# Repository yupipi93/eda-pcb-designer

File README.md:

<div align="center">

# eda-pcb-designer

**One YAML file in → a fabricable PCB out.**

A deterministic, headless **KiCad-9 PCB design pipeline** — spec → schematic →
placement → autorouting → DRC → physical verification → JLCPCB-ready gerbers —
packaged as an installable Python toolkit (`pcb-designer`), with no GUI and no
LLM in the loop.

[Quickstart](#quickstart) · [Hosted API](#3--http-api-hosted--best-for-agents-in-the-cloud) · [The verification gate](#the-physical-verification-gate) · [For AI agents](#for-ai-agents) · [Docs](#documentation)

*Lemon Piano v0.6.0 — pipeline output. Placement, routing, DRC, render and
dimension annotations all generated from one YAML file; the Arduino Nano photo
is composited pin-over-pad by the overlay stage. Designed end-to-end through
the hosted API.*

</div>

---

## The pipeline

```mermaid
flowchart LR
    Y[/"board.yaml<br/>(single source of truth)"/] --> S
    S["schematic<br/>kicad-sch-api"] --> P["place<br/>real layer flips + DRC"]
    P --> R["route<br/>freerouting + GND zone"]
    R --> D["render<br/>DIM · realistic · overlay"]
    D --> V{"verify<br/>anti-mirror gate"}
    V -->|pass| F["fab<br/>gerbers · BOM · pos · zip"]
    V -->|fail| X["⛔ no fab outputs"]
```

Every stage is **headless, idempotent and scriptable**; errors fail fast with
actionable messages. The pipeline calls **no LLM API** — it is a plain,
reproducible Python + KiCad + freerouting toolchain — but it was **built to be
driven safely by an AI coding agent** (Claude, GPT, Gemini, …) as well as by
humans: the agent edits the YAML and drives the CLI, and it cannot reach `fab`
without passing DRC plus a physical-verification gate. See
[`AGENTS.md`](AGENTS.md) for the agent operating protocol.

> [!TIP]
> **🌐 Live hosted API** — **https://pcb-designer.scv.multitecua.com** — no install
> needed. Upload a `.kicad_pcb`, get back an autorouted board, a DRC report,
> raytraced renders or a JLCPCB-ready fab zip:
> ```bash
> curl -F pcb=@board.kicad_pcb https://pcb-designer.scv.multitecua.com/route -o routed.kicad_pcb
> ```

## What it produces

One board, four render styles — all from the same `.kicad_pcb`, all generated
by the `render` stage:

| `bare` | `dim` |
|---|---|
|  |  |
| **`realistic`** | **`overlay`** |
|  |  |

Iterations are versioned, so a board's history reads like a filmstrip:

And it ships real hardware. The **MT1 rocket flight computer** went through
**5 fabricated releases at JLCPCB** — designed entirely by this pipeline inside
the [multi-rocket-avionica](https://github.com/Multitec-UA/multi-rocket-avionica)
project, and vendored here as the worked example ([`projects/mt1/`](projects/mt1/)):

| Pipeline render | The fabricated board |
|---|---|
|  |  |
| *MT1 v0.1.4 — overlay render with real breakout photos* | *The same design, fabricated at JLCPCB and populated* |

## Why

Iterating a PCB by hand in a GUI is slow and unreproducible; letting a generative
model emit `.kicad_pcb` S-expressions directly is dangerous. This toolkit takes a
third path:

- **One YAML per board** captures everything a layout iteration needs (outline,
  placements, pin counts, net numbers, trace widths) — reviewable in a diff.
- **The engine does the mechanical work deterministically**: footprint placement
  with genuine layer flips, freerouting-based autorouting, GND zone + stitching,
  DRC, versioned renders, gerber/BOM/pos exports.
- **Idempotency is law**: any stage can be re-run and converges to the same board.
- **Verification is part of the pipeline, not an afterthought** — see
  [the physical-verification gate](#the-physical-verification-gate) below.

## Install

```bash
git clone https://github.com/yupipi93/eda-pcb-designer
cd eda-pcb-designer
python3 -m venv .venv && source .venv/bin/activate
pip install -e '.[schematic,render,verify,dev]'
pcb-designer --help
```

### System requirements per stage

| Stage | Needs |
|---|---|
| `validate`, `gallery`, `init` | Python ≥ 3.11 only |
| `schematic` | `kicad-sch-api` (extra) + KiCad 9 symbol libraries |
| `place`, `render` | **KiCad 9** (`kicad-cli`) + `poppler-utils` + Pillow |
| `route` | KiCad 9 (`pcbnew` Python module) + **Java 21** + freerouting JAR |
| `verify` | numpy + Pillow (extras) |
| `export3d` | KiCad 9 (`kicad-cli`); component bodies need `kicad-packages3d` (or `--fetch-models`) |
| `fab` | KiCad 9 (`kicad-cli`) |

KiCad 9 install options are documented in [`docs/SETUP.md`](docs/SETUP.md)
(AppImage without root, or `ppa:kicad/kicad-9.0-releases`). The freerouting JAR
is **not** committed — fetch it once, checksum-verified:

```bash
./vendor/fetch-freerouting.sh    # → vendor/freerouting.jar (v2.1.0, 64 MB)
```

**Zero-install alternative** — the Docker image ships the whole toolchain
(KiCad 9 + Java 21 + freerouting + poppler):

```bash
docker build -t eda-pcb-designer .
docker run --rm -w /app eda-pcb-designer pipeline --config examples/mt1.yaml --stages place,render
```

## Quickstart

### 1 · Run the worked example (MT1 flight computer)

```bash
pcb-designer validate --config examples/mt1.yaml
# → OK: MT1 Flight Computer Board (v0.1.4) — 19 placements, 16 through-hole, 100×30 mm board

pcb-designer pipeline --config examples/mt1.yaml --stages place,route,render
# place    → placement + layer flips + GND zone + DRC + renders
# route    → freerouting autoroute + zone fill + stitches (needs Java 21 + JAR)
# render   → PCB-editor-style DIM PNGs                    (needs kicad-cli + pdftocairo)
# export3d → GLB + STEP you can rotate (see "Look at the board in 3D" below)

pcb-designer fab --config examples/mt1.yaml --version v0.1.4
# → projects/mt1/releases/v0.1.4/…zip  (9 gerbers + 2 drill + BOM + pos, JLCPCB-ready)
```

### 2 · Start your own board

```bash
pcb-designer init my-board --template minimal --vendor MyOrg
# → projects/my-board/{kicad,tools,renders,validation,releases}/
# → projects/my-board/my-board.yaml       (the board's single source of truth)
```

Then: create the KiCad project in `projects/my-board/kicad/`, fill in the YAML
(schema: [`docs/CONFIG_REFERENCE.md`](docs/CONFIG_REFERENCE.md), placement
method: [`docs/PLACEMENT_GUIDE.md`](docs/PLACEMENT_GUIDE.md)), and add the
board's orchestrator scripts under `projects/my-board/tools/` — thin wrappers
that bind your board's constants and delegate to the `pcb_designer` package
([`projects/mt1/tools/`](projects/mt1/tools/) is the reference implementation).

### 3 · HTTP API (hosted — best for agents in the cloud)

The stateless HTTP API exposes the engine operations over uploaded board
files — no project checkout, no local KiCad. **No uploaded code is ever
executed**; the server only performs KiCad file surgery and returns the
artefact.

```bash
URL=https://pcb-designer.scv.multitecua.com

# Freerouting-as-a-service: autoroute any .kicad_pcb
curl -F pcb=@board.kicad_pcb "$URL/route" -o routed.kicad_pcb

# DRC report / raytraced renders / JLCPCB-ready fab zip
curl -F pcb=@board.kicad_pcb "$URL/drc" | jq .by_severity
curl -F pcb=@board.kicad_pcb "$URL/render?side=both" -o renders.zip
# render styles: bare | realistic | realistic-dim | dim | overlay
# (overlay: client sends module photos: -F modules=@modules.yaml -F images=@nano.png)

# Rotatable 3D model (?format=glb|step|both) — the service ships the 3D model
# library, so component bodies always resolve here:
curl -F pcb=@board.kicad_pcb "$URL/export3d?format=glb" -o board.glb
curl -F pcb=@board.kicad_pcb "$URL/render?side=top&style=realistic" -o top.png
curl -F pcb=@board.kicad_pcb -F sch=@board.kicad_sch "$URL/fab?version=v1.0.0" -o release.zip

# Validate a YAML config / apply placements
curl --data-binary @examples/mt1.yaml "$URL/validate"
curl -F pcb=@board.kicad_pcb -F config=@board.yaml "$URL/place" -o placed.kicad_pcb
```

`GET /openapi.json` serves the OpenAPI 3 spec (agents self-configure from it);
binary responses become base64 JSON with `?format=json`. Run it yourself with
`make docker-api` or deploy with [`deploy/`](deploy/) (Cloud Run-ready —
production deploys are tag-driven: pushing `pcb-designer-vX.Y.Z` builds and
rolls out automatically via the multitec Terraform repo).

> The **Lemon Piano v0.6.0** board in the hero image was designed end-to-end
> through exactly these endpoints (`/place /route /drc /render /fab`) from its
> product repo, [arduino-lemon-piano](https://github.com/yupipi93/arduino-lemon-piano).

### 4 · Python API

```python
from pcb_designer import load_config
from pcb_designer.placement import place_and_flip

cfg = load_config("examples/mt1.yaml")
text = open(cfg.pcb_path("."), encoding="utf-8").read()
text, updated, missing = place_and_flip(text, {r: p.as_tuple() for r, p in cfg.placements.items()})
```

Every module is importable on its own: `kicad_pcb_io` (depth-aware S-expression
surgery), `placement` (genuine layer flips), `injection`, `routing`,
`autorouter`, `render_dim`, `render_overlay`, `export3d`, `verify`, `fab`.

## The physical-verification gate

The `verify` stage is a **hard gate between routing and fabrication**: a
computer-vision + geometric check that catches mirrored or pin-swapped
footprints by comparing the rendered board against the board's ground-truth
pinout. It exists because **three mirror bugs once reached a real fab order**
(the full story:
[`projects/mt1/docs/POST-MORTEM-001-mirror-rootcause.md`](projects/mt1/docs/POST-MORTEM-001-mirror-rootcause.md)).

| Mounting-hole CV check | Pins-over-pads check |
|---|---|
|  |  |
| *Detected hole centres vs ground truth — deviation 0.000 mm* | *Every module pin proven to sit on its pad* |

If the layout contradicts the ground truth, `verify` exits non-zero and `fab`
never runs. The mirrored board that motivated the gate is kept as a regression
fixture ([`tests/fixtures/mt1-pcb-v0.1.1-buggy.kicad_pcb`](tests/fixtures/)) so
the tests prove the gate still catches it.

## Look at the board in 3D

`export3d` runs in the default pipeline and writes two files per version:
a **`.glb`** (binary glTF — opens in browsers and light viewers) and a
**`.step`** (FreeCAD / Fusion, enclosure design, real fit checks). Both include
tracks, pads, zones, silkscreen and soldermask.

<details>
<summary><b>Viewer recommendations (VS Code, web, native) and the missing-bodies gotcha</b></summary>

**In VS Code — one click.** The repo ships a `.vscode/extensions.json`
recommending [`thingraph.cad-viewer`](https://marketplace.visualstudio.com/items?itemName=thingraph.cad-viewer),
so VS Code offers to install it the first time you open the workspace. Then
double-click the `.glb` — or the `.step` — and drag to rotate. It bundles
`occt-import-js.wasm` (OpenCascade), so its STEP support is a real geometry
kernel.

**Web, nothing to install.** Open <https://3dviewer.net> and drag the `.glb`
in — it renders in your browser, the file is not uploaded to a server.

**Local, lightweight.** [f3d](https://f3d.app) (`sudo apt install f3d`) is a
fast native viewer. There is also KiCad's own 3D viewer (**Alt+3**) if you have
KiCad installed.

**If parts are missing bodies:** component bodies are **not** in the
`.kicad_pcb` — each footprint stores a *path* into the `kicad-packages3d`
library (several GB), and `kicad-cli` skips models it cannot resolve
**silently**. `export3d` detects this and can fetch just the handful of files
your board references (~1–2 MB):

```bash
pcb-designer export3d --config board.yaml --fetch-models
```

The hosted API needs none of this — its image ships the model library.

</details>

## Architecture

```
eda-pcb-designer/
├── src/pcb_designer/        ← the installable package (board-agnostic algorithms)
│   ├── cli.py               ← `pcb-designer` console script
│   ├── config.py            ← ProjectConfig + YAML loader (typed)
│   ├── kicad_pcb_io.py      ← paren-walker primitives for .kicad_pcb surgery
│   ├── placement.py         ← place + genuine F.Cu↔B.Cu flips (mirror-safe)
│   ├── injection.py, routing.py, geometry.py, schematic.py
│   ├── autorouter.py        ← DSN → freerouting → SES → zone fill
│   ├── render_dim.py, export3d.py, fab.py, pipeline.py
│   ├── api.py               ← stateless HTTP API (Flask; `[api]` extra)
│   ├── render_overlay/      ← photorealistic overlay compositor (+ CLI)
│   ├── verify/              ← anti-mirror / anti-pin-swap / mounting-hole gate
│   └── templates/           ← `pcb-designer init` scaffolds
├── deploy/                  ← Cloud Run image (gunicorn) + Cloud Build config
├── docs/                    ← methodology corpus (see below)
├── examples/                ← board configs (mt1.yaml, blank-board)
├── projects/mt1/            ← WORKED EXAMPLE: kicad sources, tools, renders,
│                              validation evidence, fabricated release v0.1.4
├── themes/                  ← KiCad DIM render color themes
├── vendor/                  ← freerouting fetch script (JAR not committed)
└── tests/                   ← unit tests (config, verify, holes, pins, api, 3d)
```

The package/example split is the core design rule: **algorithms live in
`src/pcb_designer/` and take every parameter explicitly; board specifics live in
the board's YAML + `projects/<board>/tools/`**. The pipeline stages
subprocess-call the board's orchestrator scripts (resolved via `project.tools_dir`
in the YAML), so adding a second board never touches the package.

**Where boards live**: a real board belongs to its PRODUCT's repo under
`pcb/` — config, docs, tools, ground-truth, kicad sources, renders,
validation evidence and releases all together — with the board's tools
importing this toolkit as a sibling repo (`../eda-pcb-designer/src`) and
running the generative steps in this repo's Docker image. That is how MT1
lives upstream (`multi-rocket-avionica/pcb/`) and how the Lemon Piano board
lives in `arduino-lemon-piano/pcb/`. The `projects/mt1/` copy here is the
vendored worked example the docs and tests reference — scaffold with
`pcb-designer init`, then move the project folder into the product repo's `pcb/`.

## For AI agents

This repo is designed to be operated by an AI coding agent under a strict
protocol — the agent edits the YAML config and drives the CLI; it never
hand-edits S-expressions for routine iterations, and it cannot reach `fab`
without passing DRC + the physical-verification gate.

- **Entry point**: [`AGENTS.md`](AGENTS.md) — operating manual (reading order,
  hard rules, the iteration loop, stop-and-ask criteria).
- **Per-iteration briefing template**: [`docs/AI_AGENT_PROMPT.md`](docs/AI_AGENT_PROMPT.md).
- **Load-bearing rules**: [`docs/LESSONS_LEARNED.md`](docs/LESSONS_LEARNED.md) —
  24 rules learned from real incidents; breaking them produces boards that pass
  DRC yet crash pcbnew or ship mirrored.

## Documentation

| Doc | What it covers |
|---|---|
| [`docs/METHODOLOGY.md`](docs/METHODOLOGY.md) | The canonical 8-step iteration loop |
| [`docs/CONFIG_REFERENCE.md`](docs/CONFIG_REFERENCE.md) | Full YAML schema |
| [`docs/PLACEMENT_GUIDE.md`](docs/PLACEMENT_GUIDE.md) | How to author a placements table |
| [`docs/LESSONS_LEARNED.md`](docs/LESSONS_LEARNED.md) | 24 load-bearing rules (⭐ read first) |
| [`docs/CONVENTIONS.md`](docs/CONVENTIONS.md) | Naming / footprint / DRC conventions |
| [`docs/PIPELINE.md`](docs/PIPELINE.md) | Stage I/O map + coordinate frames |
| [`docs/MOUNTHOLE_OVERLAY_METHODOLOGY.md`](docs/MOUNTHOLE_OVERLAY_METHODOLOGY.md) | Overlay calibration + mounting-hole verification |
| [`docs/SETUP.md`](docs/SETUP.md) | Machine setup (KiCad 9, Java 21, kicad-mcp) |
| [`docs/FAB_ORDER_GUIDE.md`](docs/FAB_ORDER_GUIDE.md) | JLCPCB quote-to-order walkthrough (real MT1 order) |

> Parts of the methodology corpus are written in Spanish (the project's working
> language); code, identifiers and the agent-facing entry points are in English.

## Development

```bash
make dev    # editable install with all extras
make lint   # ruff check src tests
make test   # pytest
make docker # build the pipeline-in-a-box image
```

CI runs lint + tests on Python 3.11/3.12, validates the example configs,
round-trips a `pcb-designer init` scaffold, builds the Docker image and runs
the MT1 `place,render` stages inside it with a real KiCad 9, and smoke-tests
every HTTP API endpoint against the deploy image.

## Related projects

| repo | what |
|---|---|
| [eda-wirewright](https://github.com/yupipi93/eda-wirewright) | The sibling tool: declarative **wiring-diagram** engine with auto-router + DRC, same engine + hosted-API + agent-protocol pattern |
| [multi-rocket-avionica](https://github.com/Multitec-UA/multi-rocket-avionica) | Where this toolkit was born — the MT1 flight computer's product repo |
| [arduino-lemon-piano](https://github.com/yupipi93/arduino-lemon-piano) | Second production board (`pcb/`), designed end-to-end through the hosted API |

## License

MIT — see [`LICENSE`](LICENSE).

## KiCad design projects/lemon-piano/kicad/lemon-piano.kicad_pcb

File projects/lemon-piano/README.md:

# Lemon Piano V5.5 Board

A fabricable 2-layer KiCad-9 PCB that replaces the
[arduino-lemon-piano](../../../arduino-lemon-piano) **V5.5** breadboard
build — same circuit, same firmware pinout, nothing invented. Seven lemon
touch keys, a ten-LED progress bar, two sensitivity buttons, a passive
buzzer, and the V5.5 **power-entry filter** (TVS + Schottky + CLC pi) that
keeps mains transients from playing phantom notes on a 15–20 mV touch
margin.

| | |
|---|---|
| Top |  |
| Bottom |  |

## At a glance

| Item | Value |
|---|---|
| Outline | 100 × 30 mm, 2-layer FR4, MT1 coordinate frame (x 90–190, y 100–130) |
| MCU | Arduino Nano (ATmega328P), **socketed** — 2×15-pin 2.54 mm rows, mini-USB faces the WEST edge (flash access; USB 5 V stays behind the 1N5817) |
| Keys | 7 lemon lines (A0–A6, 220 Ω pull-ups on B.Cu) + GND clip → labelled 1×8 header, NORTH edge (`G 7 6 5 4 3 2 1`) |
| Display | 10 × 3 mm green LEDs (D2–D11), one ascending run on the SOUTH edge, 220 Ω each on B.Cu |
| Controls | SENS+ (D12) / SENS− (A7 + 10 k pull-up) buttons, SOUTH-east |
| Sound | passive buzzer on D13 |
| Power | `5V IN` screw terminal → P6KE6.8A TVS → 1N5817 → 470 µF‖100 nF → 100 µH → 470 µF‖100 nF → +5 V rail (≈4.7 V, fc ≈ 730 Hz) |
| GND | full B.Cu zone, solid connect on every GND pad, auto island-healing |
| Mounting | 2 × M2 (Ø2.5 drill / Ø5.0 pad+vias) at (95,115) & (185,115) — mirror-symmetric about x=140 |
| Status (v0.1.0) | DRC **0/0/0** · ERC 0/0 · verify_placement / verify_holes / geometry_gate ALL PASS |
| Release | [`releases/v0.1.0/lemon-piano-v0.1.0-fab.zip`](releases/v0.1.0/) — gerbers, drill, BOM, positions |

Netlist ground truth: [docs/NETLIST.md](docs/NETLIST.md) ·
decisions: [docs/DECISIONS.md](docs/DECISIONS.md) ·
state + iteration log: [docs/DESIGN_STATE.md](docs/DESIGN_STATE.md) ·
render history: [renders/INDEX.md](renders/INDEX.md)

## How to regenerate

Everything is generated from [`lemon-piano.yaml`](lemon-piano.yaml) +
[`docs/NETLIST.md`](docs/NETLIST.md); the cloud service does every
pipeline operation that has an endpoint, the Docker image handles the two
generative steps (board/schematic instantiation) and the width/zone
post-pass:

```bash
# one full iteration: build → /place → /route → post → /drc → /render → gates
./projects/lemon-piano/tools/cloud_pipeline.sh v0.1.0

# release (adds cloud /fab, writes releases/<ver>/):
./projects/lemon-piano/tools/cloud_pipeline.sh v0.1.0 --fab

# individual gates:
python3 projects/lemon-piano/tools/verify_placement.py   # anti-mirror/pin-swap
python3 projects/lemon-piano/tools/verify_holes.py       # anchor holes vs GT
python3 projects/lemon-piano/tools/geometry_gate.py      # outline/symmetry/copper
```

All builders are idempotent — re-running produces byte-identical files
(LESSONS_LEARNED §7). The KiCad artefacts live in `kicad/`; every
iteration's DRC report and renders are archived under `validation/` and
`renders/` with their version tag.

## Assembly notes

- Small passives are 0805 HandSolder; R1–R7/R18 and R8–R17 + C2/C4 mount
  on the **bottom** (refs on F.Fab, values in the BOM/pos files).
- Feed `5V IN` from a USB wall charger or bench supply — never the PC
  that flashes the Nano (see the V5.5 powering rules); loop the input
  lead 3–4 turns through a clip-on ferrite for the common-mode path.
- The GND terminal position (`G`, west end of the keys header) is the
  player's hand-held clip line.

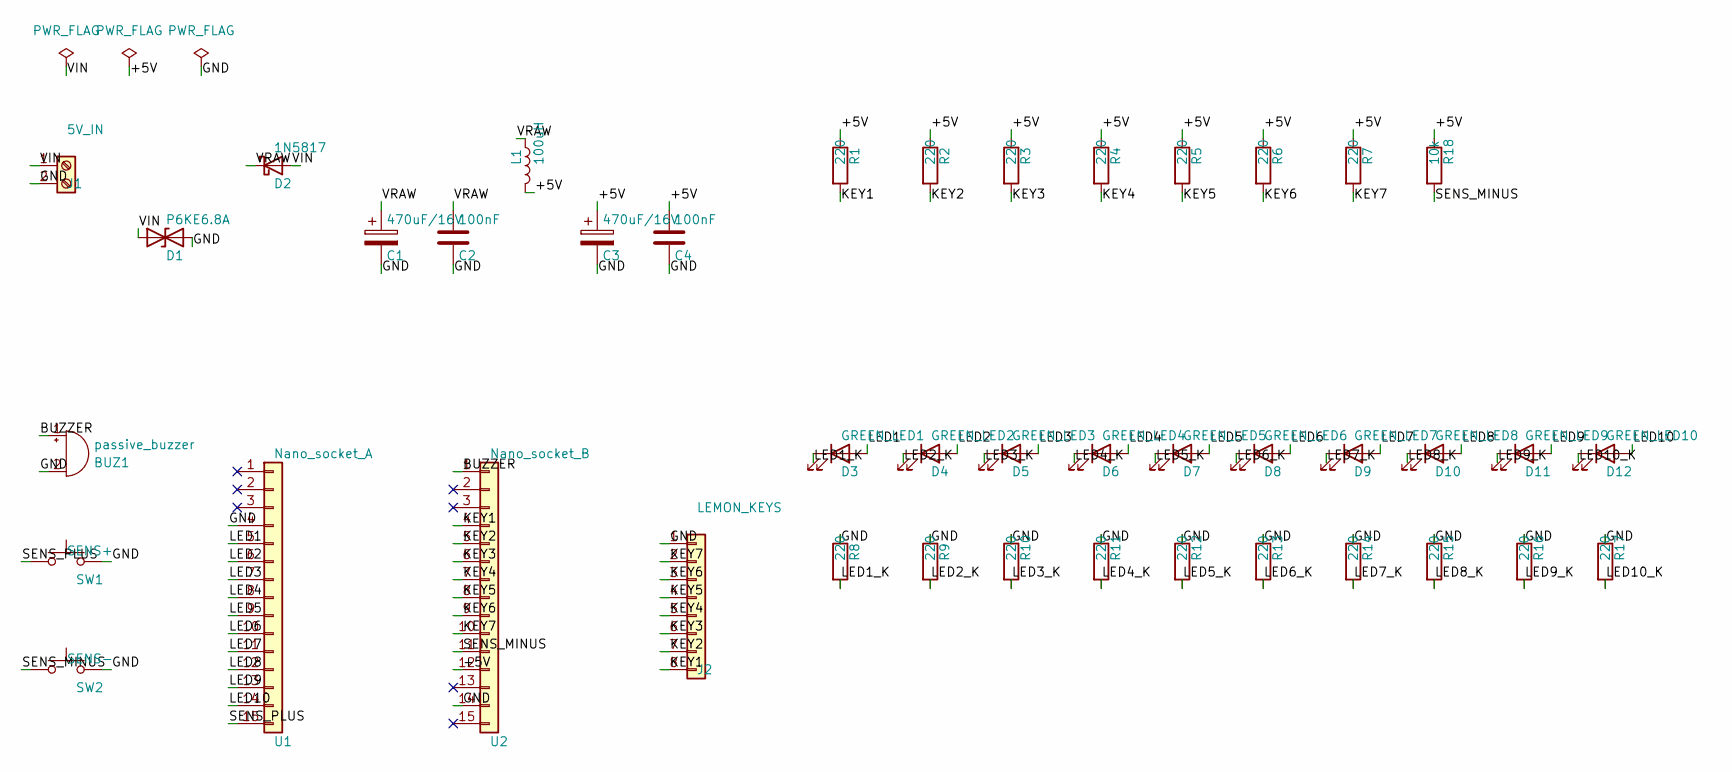
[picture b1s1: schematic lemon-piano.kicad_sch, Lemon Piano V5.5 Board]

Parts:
BUZ1: passive_buzzer; Buzzer_12x9.5RM7.6
C1, C3: 470uF/16V; CP_Radial_D8.0mm_P3.50mm
C2, C4: 100nF; C_0805_2012Metric_Pad1.18x1.45mm_HandSolder
D1: P6KE6.8A; D_DO-15_P5.08mm_Vertical_KathodeUp
D2: 1N5817; D_DO-41_SOD81_P5.08mm_Vertical_AnodeUp
D3: GREEN_LED1; LED_D3.0mm
D4: GREEN_LED2; LED_D3.0mm
D5: GREEN_LED3; LED_D3.0mm
D6: GREEN_LED4; LED_D3.0mm
D7: GREEN_LED5; LED_D3.0mm
D8: GREEN_LED6; LED_D3.0mm
D9: GREEN_LED7; LED_D3.0mm
D10: GREEN_LED8; LED_D3.0mm
D11: GREEN_LED9; LED_D3.0mm
D12: GREEN_LED10; LED_D3.0mm
J1: 5V_IN; TerminalBlock_Phoenix_MKDS-1,5-2-5.08_1x02_P5.08mm_Horizont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
J2: LEMON_KEYS; PinHeader_1x08_P2.54mm_Vertical
L1: 100uH; L_Radial_D8.7mm_P5.00mm_Fastron_07HCP
R1, R2, R3, R4, R5, R6, R7, R8, R9, R10, R11, R12, R13, R14, R15, R16, R17: 220; R_0805_2012Metric_Pad1.20x1.40mm_HandSolder
R18: 10k; R_0805_2012Metric_Pad1.20x1.40mm_HandSolder
SW1: SENS+; SW_PUSH_6mm
SW2: SENS-; SW_PUSH_6mm
U1: Nano_socket_A; PinSocket_1x15_P2.54mm_Vertical
U2: Nano_socket_B; PinSocket_1x15_P2.54mm_Vertical

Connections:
/+5V: C3.1, C4.1, L1.2, R1.1, R2.1, R3.1, R4.1, R5.1, R6.1, R7.1, R18.1, U2.12
/BUZZER: BUZ1.1 (+), U2.1
/GND: BUZ1.2 (-), C1.2, C2.2, C3.2, C4.2, D1.2 (A2), J1.2, J2.1, R8.1, R9.1, R10.1, R11.1, R12.1, R13.1, R14.1, R15.1, R16.1, R17.1, SW1.2, SW2.2, U1.4, U2.14; also elsewhere on the board
/KEY1: J2.8, R1.2, U2.4
/KEY2: J2.7, R2.2, U2.5
/KEY3: J2.6, R3.2, U2.6
/KEY4: J2.5, R4.2, U2.7
/KEY5: J2.4, R5.2, U2.8
/KEY6: J2.3, R6.2, U2.9
/KEY7: J2.2, R7.2, U2.10
/LED1: D3.2 (A), U1.5
/LED1_K: D3.1 (K), R8.2
/LED2: D4.2 (A), U1.6
/LED2_K: D4.1 (K), R9.2
/LED3: D5.2 (A), U1.7
/LED3_K: D5.1 (K), R10.2
/LED4: D6.2 (A), U1.8
/LED4_K: D6.1 (K), R11.2
/LED5: D7.2 (A), U1.9
/LED5_K: D7.1 (K), R12.2
/LED6: D8.2 (A), U1.10
/LED6_K: D8.1 (K), R13.2
/LED7: D9.2 (A), U1.11
/LED7_K: D9.1 (K), R14.2
/LED8: D10.2 (A), U1.12
/LED8_K: D10.1 (K), R15.2
/LED9: D11.2 (A), U1.13
/LED9_K: D11.1 (K), R16.2
/LED10: D12.2 (A), U1.14
/LED10_K: D12.1 (K), R17.2
/SENS_MINUS: R18.2, SW2.1, U2.11
/SENS_PLUS: SW1.1, U1.15
/VIN: D1.1 (A1), D2.2 (A), J1.1
/VRAW: C1.1, C2.1, D2.1 (K), L1.1

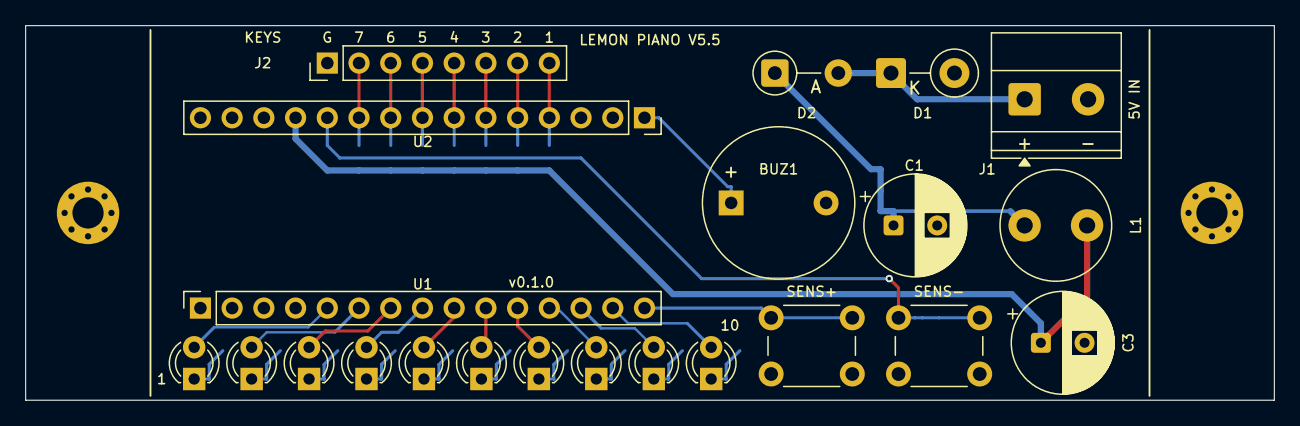
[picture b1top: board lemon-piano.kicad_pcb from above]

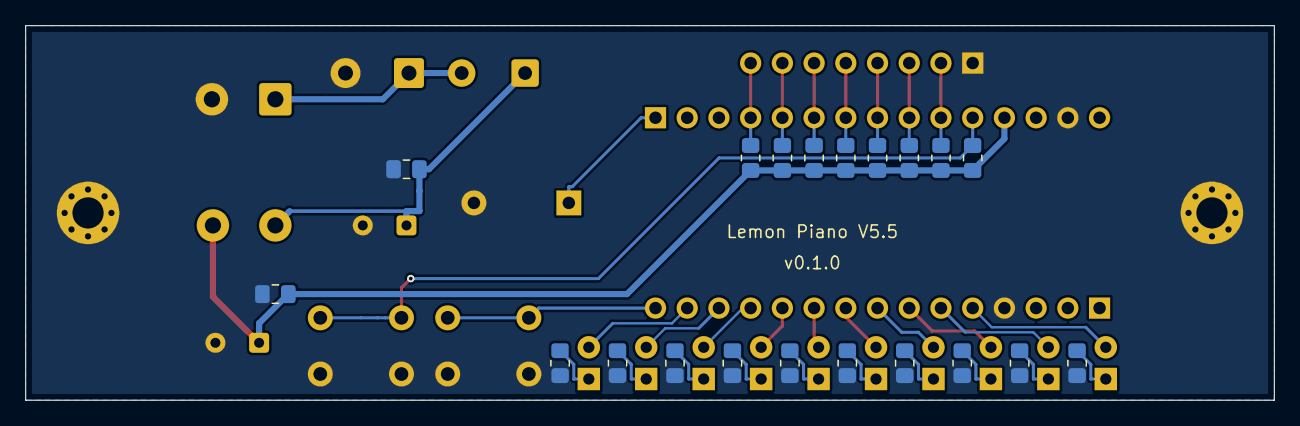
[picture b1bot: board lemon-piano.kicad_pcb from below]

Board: 2 copper layers, 100.0 x 30.0 mm, 44 parts (20 on the bottom side), 34 nets.

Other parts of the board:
H1, H2: M2; MountingHole_2.5mm_Pad_Via

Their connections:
/GND: H1.1, H2.1; also elsewhere on the board

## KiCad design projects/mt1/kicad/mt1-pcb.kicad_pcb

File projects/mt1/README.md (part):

# MT1 — Flight Computer Board

> **Nota**: este directorio es el *worked example* del toolkit standalone [`eda-pcb-designer`](../../README.md), extraído del repo upstream `multi-rocket-avionica`. Aquí se conserva únicamente el último release (**v0.1.4**) con sus renders y evidencia de validación; el historial completo de iteraciones (CHANGELOG, DECISIONS, QUESTIONS, compras/inventario, ~20 iteraciones de renders) vive upstream en [github.com/Multitec-UA/multi-rocket-avionica](https://github.com/Multitec-UA/multi-rocket-avionica) bajo `pcb/projects/mt1/`.

MultitecUA's open-source rocket avionics PCB for the **SURT × SpainRocketry L1 launch (2026-07-18/19)**. 100 × 30 mm KiCad-9 board with a XIAO ESP32-S3 Plus, LSM6DSO32 IMU (±32 g), BMP585 barometer, microSD breakout, y un subsistema de batería v0.1.0 con switch de armado, jumper externo y sensor de voltaje on-board. Diseñado end-to-end con el toolkit reusable [`pcb-designer`](../../) — MT1 es su ejemplo dogfood.

## At a glance

| | |
|---|---|
| Current revision | **v0.1.4** (fabricada 2026-06-18; v0.1.0-battery-power fue el primer release fabricado) |
| Board size | 100 × 30 mm (10 mm left anchor + 70 mm electronic + 20 mm right anchor) |
| Estimated weight | ~38 g (PCB + populated breakouts + battery) |
| MCU | Seeed XIAO ESP32-S3 Plus (240 MHz, 8 MB PSRAM, WiFi + BLE) |
| IMU | Adafruit LSM6DSO32 (±32 g, ±2000 °/s) |
| Barometer | Adafruit BMP585 (30 – 1250 hPa, ±0.06 hPa) |
| Storage | microSD breakout (SDIO 1-bit) |
| Battery | LiPo 602535 1S 500 mAh, JST-PH 2 mm |
| Battery management | SW1 SPDT (armado) + J2 (jumper externo paralelo) + R3/R4 + C8 (sensor VBAT_SENSE → D0/ADC1_CH0) |
| Footprints v0.1.0 | 19 (5 sockets módulos + J4 proto + 6 mounting holes + 7 subsistema batería) |
| Last ERC | ✅ 0 errors, 0 warnings (v0.1.0, 2026-05-22) |
| Last DRC | ✅ 0 errores · 0 unconnected · 77 warnings cosméticos (v0.1.4, 2026-06-18) — full report en [`validation/drc-v0.1.4.json`](validation/drc-v0.1.4.json) |
| Tests | ✅ 42/42 (v0.1.4) |
| Fab status | ✅ v0.1.4 empaquetada para fab (gerbers + drill + BOM + pos en [`releases/v0.1.4/`](releases/v0.1.4/)); pedido v0.1.0: JLCPCB 5 boards + LCSC `WM2605230017` (histórico, en el repo upstream) |

## Renders v0.1.4

### Vista DIM (PCB-editor-style, alta nitidez de trazas)

| Front (F.Cu) | Back (B.Cu) |
|:---:|:---:|
|  |  |

Renders auto-generados por [`tools/render_dim.py`](tools/render_dim.py) con themes en [`themes/dim-{front,back}.json`](../../themes/). En *dim-front* la cara F.Cu se ve nítida (rojo) sobre fondo oscuro; en *dim-back* es la B.Cu (cian) la prominente. El plano GND continuo de la B.Cu llena toda la cara inferior con thermal reliefs alrededor de los pads GND.

### Vista 3D fotorrealista (KiCad pcbnew + overlay)

| Top | Bottom |
|:---:|:---:|
|  |  |

Composición de [`src/pcb_designer/render_overlay/cli.py`](../../src/pcb_designer/render_overlay/cli.py) que toma los renders 3D base y superpone fotos físicas de los breakouts (XIAO, microSD en top; LSM6, BMP585 en bottom). El config de módulos vive en [`overlays/modules.yaml`](overlays/modules.yaml) y las fotos en `overlays/component-images/`. **Obligatorio** para cualquier entregable v0.X.X (regla MultitecUA).

### Vistas 3D sin overlay

Renders crudos en [`renders/`](renders/): `v0.1.4-top.png` y `v0.1.4-bottom.png`. Catálogo en [`renders/INDEX.md`](renders/INDEX.md) — el histórico completo (~16 versiones × 4 vistas) vive en el repo upstream —, regenerable con `pcb-designer gallery --renders-dir projects/mt1/renders`.

## Cómo está organizado el board

### Mapa físico (vista top)

```
                            x=100              x=170
       LEFT ANCHOR (x=90)   │  ELECTRONIC ZONE  │  RIGHT ANCHOR (x=190)
              │             │   70 × 30 mm      │             │
   y=100  ┌───┴───┬─────────┴───────────────────┴─────────┬───┴───┐
          │       │ ░░░ BATTERY STRIP (y=104) ░░░ ░░░░░░░ │       │
          │       │ J1   SW1   J2   R3 R4 C8   J5        │  H1   │
          │       │ JST  ON   ext  ╰─VBAT_SENSE╯  → BAT+ │  H2   │
          │       │                                       │       │
          │  H5   │            J4 proto (8-pin)           │       │
          │       │                                       │       │
          │       │           U1 XIAO  U5 XIAO            │  H3   │
          │       │           (left)   (right)            │  H4   │
          │       │             ╰─ U4 microSD ─╯          │       │
          │  H6   │                                       │       │
   y=130  └───┬───┴───────────────────────────────────────┴───┬───┘
              │              ↑ service edge                   │
                          (USB-C XIAO + microSD slot
                           asoman por aquí)
```

En B.Cu (vista trasera) sólo cuelgan **U2 (LSM6DSO32 IMU)** alineado con el eje longitudinal del cohete y **U3 (BMP585 barómetro)** en la esquina contraria. El resto de la cara es plano GND continuo (`(zone)` rellenado por `ZONE_FILLER` con thermal reliefs).

### Bloques funcionales

```mermaid
flowchart LR
  LIPO[("LiPo 602535<br/>500 mAh")]
  J1[("J1 JST-PH<br/>battery in")]
  SW1{{"SW1 SPDT<br/>(arming)"}}
  J2{{"J2 1×2<br/>(ext jumper)"}}
  J5[("J5 1×2<br/>→ XIAO BAT+")]
  XIAO["U1+U5 XIAO ESP32-S3 Plus<br/>(MCU socket, 14 pines útiles)"]
  IMU["U2 LSM6DSO32 (B.Cu)<br/>I²C ±32 g IMU"]
  BARO["U3 BMP585 (B.Cu)<br/>I²C barómetro"]
  SD["U4 microSD<br/>SDIO 1-bit"]
  ADC{{"D0 ADC1_CH0<br/>VBAT_SENSE"}}
  PROTO["J4 1×8 proto<br/>(D1-D3 libres + DBG + 3V3 + GND)"]

  LIPO --> J1
  J1 -- BAT_P --> SW1
  J1 -- BAT_P --> J2
  SW1 -- BAT_SW --> J5
  J2 -- BAT_SW --> J5
  J5 -- "BAT+" --> XIAO
  SW1 -- BAT_SW --> ADC
  XIAO -- "+3V3" --> IMU & BARO & SD
  XIAO -- I²C --> IMU & BARO
  XIAO -- SDIO --> SD
  XIAO -- pins libres --> PROTO
```

### Tabla de componentes (v0.1.0)

| Ref | Componente | Capa | Función |
|---|---|---|---|
| **U1** | XIAO ESP32-S3 Plus — socket izquierdo (pines D0..D6 + GND) | F.Cu | MCU. Pin 1 (= D0) → VBAT_SENSE/ADC1. USB-C asoma al borde y=130. |
| **U5** | XIAO ESP32-S3 Plus — socket derecho (pines D7..D10 + BAT+ + 3V3) | F.Cu | MCU (mismo módulo). Pin 6 = BAT+ → recibe `BAT_SW`. Pin 7 = +3V3 (regulado interno). |
| **J4** | Proto header 1×8 vertical sobre los XIAO | F.Cu | Test points + pines libres: J4.1 = VBAT_SENSE, J4.2-4 = D1..D3 libres, J4.5 = DBG_TX, J4.6 = DBG_RX, J4.7 = +3V3, J4.8 = GND. |
| **U2** | Adafruit LSM6DSO32 — IMU 6DoF ±32 g | **B.Cu** | I²C @ 0x6A. Body alineado con eje longitudinal del cohete (rot=90). |
| **U3** | Adafruit BMP585 — barómetro 30-1250 hPa | **B.Cu** | I²C @ 0x47. Junto al LSM6 para minimizar trazas I²C. |
| **U4** | microSD breakout — slot estándar | F.Cu | SDIO 1-bit. Slot asoma al borde y=130 (tarjeta se extrae sin desmontar el board). |
| **J1** | JST-PH 2-pin horizontal — entrada LiPo | F.Cu | Pin 1 = `BAT_P` (raw battery), Pin 2 = `GND`. Compatible con `LiPo 602535`. |
| **SW1** | SPDT slide switch (CK OS102011MS2Q) — armado | F.Cu | Pad 1 común = `BAT_P`. Pad 2 (throw A, ON) = `BAT_SW`. Pad 3 (throw B, OFF) = **NC** (intencionalmente). |
| **J2** | Header 1×2 vertical — bypass / botón externo | F.Cu | Paralelo a SW1: Pin 1 = `BAT_P`, Pin 2 = `BAT_SW`. |
| **J5** | Header 1×2 vertical — tap-out a XIAO | F.Cu | Pin 1 = `BAT_SW` (cable manual al pad BAT+ del XIAO en U5), Pin 2 = `GND`. |
| **R3** | 100 kΩ 0805 1% — top del divisor VBAT | F.Cu | Entre `BAT_SW` y `VBAT_SENSE`. |
| **R4** | 100 kΩ 0805 1% — bottom del divisor VBAT | F.Cu | Entre `VBAT_SENSE` y `GND`. Junto con R3 forma 1:2 ÷. |
| **C8** | 100 nF 0805 X7R 50V — filtro ADC | F.Cu | `VBAT_SENSE` ↔ `GND`. Cap RC anti-ruido en la entrada del ADC. |
| **H1..H4** | Mounting holes M2 NPTH (anchor derecho, patrón 2×2) | F.Cu | Fijación estructural al airframe (lado fijo al cohete). |
| **H5, H6** | Mounting holes M2 NPTH (anchor izquierdo, en columna) | F.Cu | Fijación estructural (lado opuesto). |

> Componentes históricos retirados en v0.0.12 (BUZ1 buzzer, SW2/SW3 botones, LED+R de UI, F1 PTC, D3 TVS, C1 22 µF, C2..C7 de decoupling, TP1..TP7 test points discretos) — catálogo + criterio de re-incorporación en `docs/REMOVED_COMPONENTS.md` (en el repo upstream).

## Sistema de alimentación detallado (v0.1.0)

Esta es la novedad principal del release v0.1.0 — antes el XIAO se alimentaba directamente desde el conector JST sin armado ni telemetría de batería. Ahora hay tres formas de controlar el encendido y una lectura analógica del voltaje de batería en tiempo real.

### Topología eléctrica

```
                    ┌───────── SW1 (ON) ─────────┐
   LiPo+ ─J1.1─ BAT_P ─┤                            ├── BAT_SW ──┬── J5.1 ──► XIAO BAT+ (U5 pin 6)
                       │                            │             │
                       └───── J2.1 ── ext ── J2.2 ──┘             │
                                                                  │
                                    ┌─── R3 100kΩ ───┬── VBAT_SENSE ──► XIAO D0 (ADC1_CH0)
                                    │                │                    │
                                    │                ├── R4 100kΩ ──┐    │
                                    │                └── C8 100nF ──┤    │ (también expuesta en
                                    │                               │    │  J4.1 como test point)
   LiPo− ─J1.2─ GND ────────────────┴───────────────────────────────┴────┴──► GND plane (B.Cu)
                                                          J5.2 ──────────┘
```

Pad-map del SW1 (footprint `SW_Slide_SPDT_Straight_CK_OS102011MS2Q`):

```
       ┌──────────────┐
   1 ──┤●  common     │   ← BAT_P (entrada desde J1.1)
   2 ──┤●  throw A    │   ← BAT_SW (cuando la barrita está en posición ON)
   3 ──┤●  throw B NC │   ← OFF: pad sin conectar (sin carga parasitaria)
       └──────────────┘
```

### 1. Switch principal SW1 (armado / disconnect)

**Componente físico**: SPDT slide switch C&K `OS102011MS2Q` THT, actuador horizontal accesible desde el borde del PCB. Se usa como **interruptor de armado**: se desliza a la posición ON el día del vuelo, off durante transporte/integración.

**Lógica**:
- Posición **ON** (barrita hacia pad 2): cierra `BAT_P` → `BAT_SW` → la batería energiza el XIAO vía J5.
- Posición **OFF** (barrita hacia pad 3): pad 3 está deliberadamente sin conectar (`NC`). El circuito de batería queda completamente abierto: cero corriente parásita en la balanza R3/R4 (el ADC no tiene a qué medir porque `BAT_SW` está flotante).

**Razón de diseño** (ADR-014, ver `docs/DECISIONS.md` en el repo upstream): un slide SPDT es preferible a un push-button latching porque (a) es visualmente inequívoco — el ojo distingue ON/OFF a distancia — y (b) no se actua por accidente con un golpe lateral. Coste: 1 € en LCSC vs 0.10 € de un push, asumido.

### 2. Jumper auxiliar J2 (bypass / botón exterior)

**Header 1×2 PinHeader 2.54 mm** colocado eléctricamente en **paralelo** a SW1: pin 1 = `BAT_P` (entrada), pin 2 = `BAT_SW` (salida).

**Tres modos de uso:**

1. **Jumper colocado**: J2 cortocircuita `BAT_P` ↔ `BAT_SW`. El sistema queda **siempre encendido** ignorando SW1. Útil en mesa para evitar tocar SW1 a cada flash/depuración.

2. **Botón exterior conectado**: a J2 se le cablean dos hilos hacia un pulsador exterior montado en el cuerpo del cohete (típicamente un pulsador estanco accesible sin desmontar la ojiva). El pulsador queda **en paralelo con SW1**, así que sirve para encender desde fuera sin desarmar nada. Cualquiera de los dos caminos cerrado → sistema activo.

3. **Vacío**: comportamiento por defecto, SW1 es el único control.

> **Nota importante sobre seguridad eléctrica**: con SW1 OFF y J2 sin jumper, el board está completamente desconectado de la batería — esto es lo que se documenta como "safe state" para integración con pirotecnia o manipulación cerca del LiPo. Para forzar el "siempre on" cuando se vuela con telemetría continua, coloca un jumper en J2 **antes** del flight.

### 3. Sensor de voltaje on-board (VBAT_SENSE)

**Objetivo**: telemetría en tiempo real del estado de carga de la batería, leíble por software sin instrumentación externa. La red `VBAT_SENSE` se conecta directamente a `D0` del XIAO (= `GPIO1`, multiplexado a `ADC1_CH0`).

**Circuito**: divisor resistivo 1:2 con filtro RC en la salida.

| Componente | Valor | Función |
|---|---|---|
| R3 | 100 kΩ 0805 1% | Rama superior del divisor (BAT_SW → VBAT_SENSE) |
| R4 | 100 kΩ 0805 1% | Rama inferior (VBAT_SENSE → GND) |
| C8 | 100 nF 0805 X7R | Cap de filtrado en VBAT_SENSE → GND |

**Cálculo del rango**:

```
V_adc = V_BAT × R4 / (R3 + R4) = V_BAT × 100k / 200k = V_BAT × 0.5

Battery range  →  ADC input voltage
  4.20 V (full)  →  2.10 V
  3.70 V (nom)   →  1.85 V
  3.30 V (cutoff) →  1.65 V
  3.00 V (deep low) →  1.50 V
```

Con el ESP32-S3 en su atenuación recomendada (`ADC_ATTEN_DB_11`, rango ≈ 0–3.1 V), todo el envolvente del LiPo cae dentro del rango lineal del ADC con margen al techo. La firma del divisor consume `4.2 V / 200 kΩ = 21 µA` constante mientras el sistema está armado (despreciable frente al consumo del XIAO, decenas de mA).

**Por qué los 100 nF de C8**: el ADC del ESP32-S3 muestrea con un capacitor interno; pico de corriente en el instante de muestreo. C8 actúa como reservorio local y promedia ruido conmutado del rail de batería (especialmente importante cuando el WiFi del XIAO entra en transmisión y mete picos de hasta 300 mA en `BAT_P`).

**Cómo leerlo en firmware** (referencia, no incluido en este repo):

```cpp
#include <driver/adc.h>
adc1_config_width(ADC_WIDTH_BIT_12);
adc1_config_channel_atten(ADC1_CHANNEL_0, ADC_ATTEN_DB_11);
int raw = adc1_get_raw(ADC1_CHANNEL_0);                 // 0..4095
float v_adc = raw * 3.1f / 4095.0f;
float v_bat = v_adc * 2.0f;                             // 1:2 divider
```

**Test point**: `VBAT_SENSE` también está expuesta en **J4.1** (primer pin del header proto sobre el XIAO), así que se puede medir con multímetro sin pinchar el divisor. Útil para calibrar el factor 0.5 contra el voltaje real de la batería al integrar el sistema.

### 4. Conexión al XIAO — J5 y los pads BAT+/BAT−

El XIAO ESP32-S3 Plus tiene en su parte trasera dos pads **TH** marcados `BAT+` y `BAT−` (cara de las pistas, no headers). El XIAO en sí no tiene un PMIC de carga ni un boost — `BAT+` va directamente a la entrada del regulador interno LDO del XIAO. Eso significa que **la batería se cablea manualmente** de J5 a esos pads con dos hilos cortos:

- **J5.1** (`BAT_SW`) → pad `BAT+` del XIAO (en U5).
- **J5.2** (`GND`) → pad `BAT−` del XIAO (en U5).

> Esta es una limitación del XIAO ESP32-S3 Plus que evaluamos al elegirlo: no tiene contactos de batería accesibles desde el header SMT principal. La opción de poner un footprint pogo o spring-loaded se descartó por coste/área. Dos hilos manuales a J5 son robustos y reversibles.

### 5. Pinout completo del XIAO en MT1

```
                    ┌──────────────────────┐
        VBAT_SENSE──┤ D0  (GPIO1, ADC1_CH0)│
                    │ D1  (GPIO2)          │── J4.2 (libre, breakout)
                    │ D2  (GPIO3)          │── J4.3 (libre, breakout)
                    │ D3  (GPIO4)          │── J4.4 (libre, breakout)
            I2C_SDA─┤ D4  (GPIO5)          │── U2 + U3 (SDA bus)
            I2C_SCL─┤ D5  (GPIO6)          │── U2 + U3 (SCL bus)
             DBG_TX─┤ D6  (GPIO7, UART)    │── J4.5
             DBG_RX─┤ D7  (GPIO20, UART)   │── J4.6
           SDIO_D0─┤ D8  (GPIO8)          │── U4 microSD DAT0
           SDIO_CLK─┤ D9  (GPIO9)          │── U4 microSD CLK
           SDIO_CMD─┤ D10 (GPIO10)         │── U4 microSD CMD
                    │                      │
              BAT+──┤ pad TH trasero       │── J5.1 (BAT_SW)
              BAT−──┤ pad TH trasero       │── J5.2 (GND)
              +3V3──┤ pin 7 (regulado int.)│── U2 + U3 + U4 (rail sensores) + J4.7
                    └──────────────────────┘
```

Las redes activas en v0.1.0 son **15** (ver `docs/DESIGN_STATE.md §3 Nets` para conteos y la traza completa). Las nets críticas en términos de ruido/longitud son I²C_SDA/SCL (sensores) y las SDIO (microSD); ambas viven en F.Cu con plano GND continuo en B.Cu actuando de retorno limpio.

## Cómo regenerar el board

El board es paramétrico: cada constante vive en [`examples/mt1.yaml`](../../examples/mt1.yaml) (sección `geometry`, `placements`, `pin_counts`, `pad_half`, `nets`, `routing`). Regenerar MT1 end-to-end es un único comando:

```bash
# (desde la raíz del repo, una vez por máquina) venv local del paquete
python3 -m venv .venv
source .venv/bin/activate
python3 -m pip install -e '.[schematic,render,dev]'

# Pipeline completo:
pcb-designer pipeline \
    --config examples/mt1.yaml \
    --stages place,route,render

# Empaquetar release (gerbers + drill + BOM + pos + zip):
pcb-designer fab \
    --config examples/mt1.yaml \
    --version v0.1.4
```

Equivalente paso-a-paso vía los orquestadores MT1 (útil para flags como `--dry-run` o `--version`):

```bash
python3 projects/mt1/tools/build_schematic.py    # regenera .kicad_sch desde spec
python3 projects/mt1/tools/inject_battery.py     # inyecta subsistema batería v0.1.0
python3 projects/mt1/tools/place_components.py   # placement + flip + DRC + 3D + DIM renders
python3 projects/mt1/tools/run_autorouter.py     # freerouting + GND zone fill
python3 projects/mt1/tools/render_dim.py --version v0.1.4
python3 src/pcb_designer/render_overlay/cli.py \
    --version v0.1.4                    # ⭐ overlay fotorrealista (obligatorio)
pcb-designer fab \
    --config examples/mt1.yaml \
    --version v0.1.4
```

El paso de overlay es **obligatorio** para cualquier entregable v0.X.X de este proyecto — nunca lo saltes.

## Contexto aerodinámico (justifica el sensor IMU)

Simulación OpenRocket en `simulation/` (en el repo upstream) del cohete MT1 (motor Cesaroni 232H123-14A) predice apogeo 586 m, velocidad pico 115 m/s, **aceleración pico 7.7 g**. El IMU se eligió con margen (LSM6DSO32 ±32 g) para que el envolvente de vuelo quede holgadamente dentro del rango lineal sin saturar.

## Inventario físico y etiquetado

`inventory-labels.html` (en el repo upstream) es un documento HTML auto-contenido (abrible en navegador) con las etiquetas imprimibles de cada bin del kit de partes. Genera un PDF de bin labels listo para pegar en cajas Hammond o sobre el banco de trabajo. El contenido del inventario "fuente de verdad" vive en `docs/INVENTORY.md` (también en el repo upstream; cantidades disponibles + códigos LCSC/Digikey + ubicación física en el laboratorio).

> Para imprimir las etiquetas: `xdg-open pcb/projects/mt1/inventory-labels.html` (desde el repo upstream) → Ctrl+P → "Save as PDF".

## Releases y fabricación

> **Nota**: el release vigente es **v0.1.4** (fabricada 2026-06-18; DRC 0 errores / 77 warnings; 42/42 tests) — ver [`releases/v0.1.4/`](releases/v0.1.4/) y sus [notas de release](releases/v0.1.4/README.md).

`releases/v0.1.0/` (histórico, en el repo upstream) contiene el primer corte fabricado:

| Archivo | Contenido |
|---|---|
| `README.md` | Notas del release (revisión, fecha, links a DRC, decisión de fab). |
| `gerbers/` | 9 capas Gerber (F/B Cu, Paste, Mask, Silkscreen, Edge Cuts) + 2 drills (NPTH, PTH) + `.gbrjob`. |
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
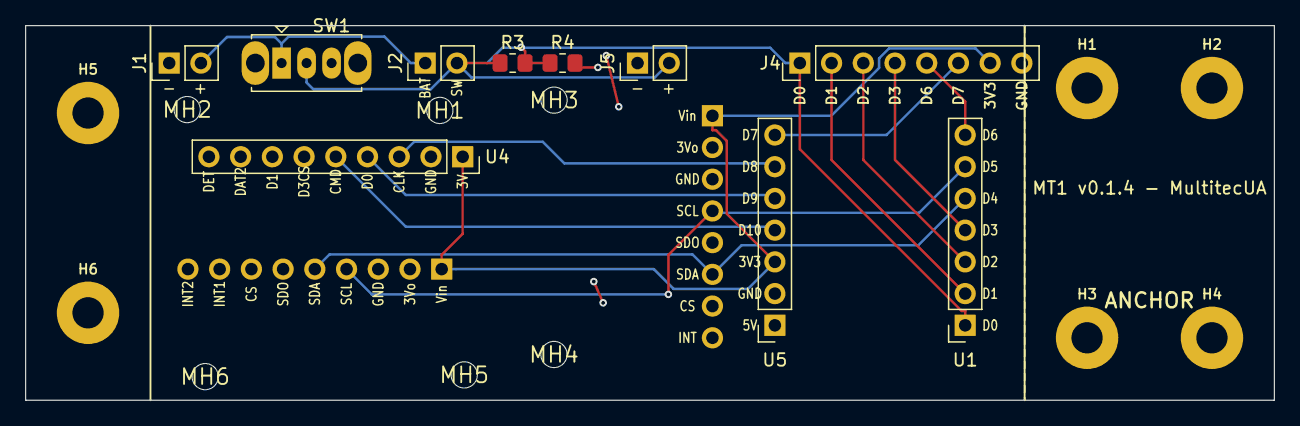
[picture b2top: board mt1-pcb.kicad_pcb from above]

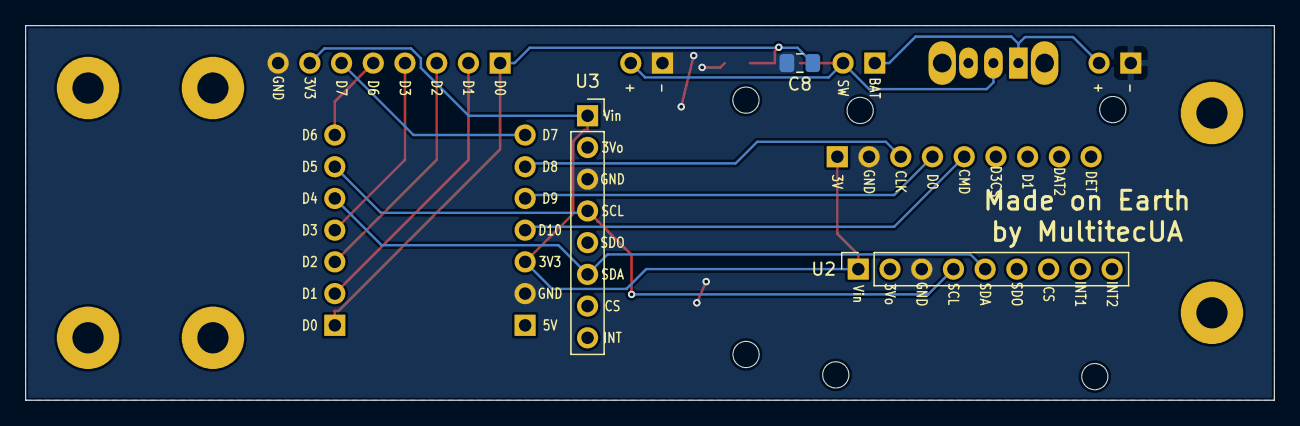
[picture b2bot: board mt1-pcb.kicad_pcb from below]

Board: 2 copper layers, 100.0 x 30.0 mm, 25 parts (3 on the bottom side), 15 nets.

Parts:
C8: C_0805_2012Metric_Pad1.18x1.45mm_HandSolder
H1, H2, H3, H4, H5, H6: MountingHole; MountingHole_2.5mm_Pad_Via
J1, J5: Conn_01x02; PinHeader_1x02_P2.54mm_Vertical
J2: PinHeader_1x02_P2.54mm_Vertical
J4: proto_header; PinHeader_1x08_P2.54mm_Vertical
MH1, MH2, MH3, MH4, MH5, MH6: MT_MountHole_M2
R3, R4: R_0805_2012Metric_Pad1.20x1.40mm_HandSolder
SW1: SW_Slide_SPDT_Straight_CK_OS102011MS2Q
U1: XIAO_left_socket; PinSocket_1x07_P2.54mm_Vertical
U2: LSM6DSO32_socket; PinSocket_1x09_P2.54mm_Vertical
U3: BMP585_socket; PinSocket_1x08_P2.54mm_Vertical
U4: microSD_socket; PinSocket_1x09_P2.54mm_Vertical
U5: XIAO_right_socket; PinSocket_1x07_P2.54mm_Vertical

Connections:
/+3V3: J4.7, U2.1, U3.1, U4.1, U5.3
/BAT_P: J1.2, J2.1, SW1.1
/BAT_SW: J2.2, J5.2, R3.1, SW1.2
/BTN2: J4.2, U1.2
/DBG_RX: J4.6, U5.7
/DBG_TX: J4.5, U1.7
/GND: C8.2, J1.1, J4.8, J5.1, R4.2, U2.3, U3.3, U4.2, U5.2
/I2C_SCL: U1.6, U2.4, U3.4
/I2C_SDA: U1.5, U2.5, U3.6
/LED1: J4.3, U1.3
/LED2: J4.4, U1.4
/SDIO_CLK: U4.3, U5.6
/SDIO_CMD: U4.5, U5.4
/SDIO_D0: U4.4, U5.5
/VBAT_SENSE: C8.1, J4.1, R3.2, R4.1, U1.1

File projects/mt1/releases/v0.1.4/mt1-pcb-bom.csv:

"Reference","Value","Footprint","QUANTITY"
"C8","100nF","Capacitor_SMD:C_0805_2012Metric_Pad1.18x1.45mm_HandSolder","1"
"J1","LiPo_battery","Connector_JST:JST_PH_S2B-PH-K_1x02_P2.00mm_Horizontal","1"
"J2","ext_switch_header","Connector_PinHeader_2.54mm:PinHeader_1x02_P2.54mm_Vertical","1"
"J4","proto_header","Connector_PinHeader_2.54mm:PinHeader_1x08_P2.54mm_Vertical","1"
"J5","XIAO_BAT_wires","Connector_PinHeader_2.54mm:PinHeader_1x02_P2.54mm_Vertical","1"
"R3,R4","100k","Resistor_SMD:R_0805_2012Metric_Pad1.20x1.40mm_HandSolder","2"
"SW1","arming_switch","Button_Switch_THT:SW_Slide_SPDT_Straight_CK_OS102011MS2Q","1"
"U1","XIAO_left_socket","Connector_PinSocket_2.54mm:PinSocket_1x07_P2.54mm_Vertical","1"
"U2","LSM6DSO32_socket","Connector_PinSocket_2.54mm:PinSocket_1x09_P2.54mm_Vertical","1"
"U3","BMP585_socket","Connector_PinSocket_2.54mm:PinSocket_1x08_P2.54mm_Vertical","1"
"U4","microSD_socket","Connector_PinSocket_2.54mm:PinSocket_1x09_P2.54mm_Vertical","1"
"U5","XIAO_right_socket","Connector_PinSocket_2.54mm:PinSocket_1x07_P2.54mm_Vertical","1"

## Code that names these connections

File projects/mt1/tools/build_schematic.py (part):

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    R3, R4 (100 kΩ 0805 HandSolder) – 1:2 divider
    C8 (100 nF 0805 HandSolder)     – RC filter at the ADC input

  Net rename: BTN1 → VBAT_SENSE. The pin used to be the BTN1 line in
  the original plan but SW2 (the button) was scoped out; D0 is now
  driven by the divider midpoint.

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        # D0 / GPIO1 / ADC1_CH0: in v0.1.0 this pin reads the LiPo voltage
        # via the R3/R4 divider midpoint (was BTN1 in pre-v0.1.0 plans).
        "1": ("VBAT_SENSE", "left"),
        "2": ("BTN2",    "left"),  # D1 / GPIO2
        "3": ("LED1",    "left"),  # D2 / GPIO3
        "4": ("LED2",    "left"),  # D3 / GPIO4
        "5": ("I2C_SDA", "left"),  # D4 / GPIO5
        "6": ("I2C_SCL", "left"),  # D5 / GPIO6
        "7": ("DBG_TX",  "left"),  # D6 / GPIO43 — routed to J4 in v0.0.14
    })

    # U5 — XIAO RIGHT header (7 pins): 5V, GND, 3V3, D10, D9, D8, D7
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        "1": (None, None),          # 5V (USB) — no consumer in slim design (NC)
        "2": ("GND",      "right"),
        "3": ("+3V3",     "right"),
        "4": ("SDIO_CMD", "right"), # D10 / GPIO9
        "5": ("SDIO_D0",  "right"), # D9  / GPIO8
        "6": ("SDIO_CLK", "right"), # D8  / GPIO7
        "7": ("DBG_RX",   "right"), # D7 / GPIO44 — routed to J4 in v0.0.14
    })

    # ==================================================================
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        # divider midpoint + XIAO D0). Probe with a multimeter to read
        # raw ADC input voltage.
        "1": ("VBAT_SENSE", "left"),
        "2": ("BTN2",   "left"),   # D1 / GPIO2 — free for a future button
        "3": ("LED1",   "left"),   # D2 / GPIO3 — free for a future LED
        "4": ("LED2",   "left"),   # D3 / GPIO4 — free for a future LED
        "5": ("DBG_TX", "left"),   # D6 / GPIO43
        "6": ("DBG_RX", "left"),   # D7 / GPIO44
        "7": ("+3V3",   "left"),
        "8": ("GND",    "left"),
    })
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    # U3 — BMP585 socket: 1x8 single row.
    # v0.1.2 (BLK-007 / POST-MORTEM-001 / ERRATA-001 §10): the Adafruit BMP585
    # header is  Vin 3Vo GND SCL [SDO] [SDA] CS INT  — SDO sits BETWEEN SCL and
    # SDA (unlike the LSM6, where SDA is pin 5). So I2C_SDA must land on pin 6
    # (real SDA), and pin 5 (SDO) stays NC (→ I2C address 0x47).
    #   1=Vin, 2=3Vo, 3=GND, 4=SCL, 5=SDO, 6=SDA, 7=CS, 8=INT
    sch.components.add(lib_id="Connector_Generic:Conn_01x08",
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        "3": ("GND", "right"),
        "4": ("I2C_SCL", "right"),
        "5": (None, None),         # SDO (NC → addr 0x47)
        "6": ("I2C_SDA", "right"), # SDA real (pin 6)
        "7": (None, None),         # CS
        "8": (None, None),         # INT
    })
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    # J1 — LiPo battery in (1x02 pin header, v0.1.3; was a JST-PH).
    # v0.1.3 (2026-06-16): converted JST→pin header to free top-strip width
    # for the module mounting holes. Polarity follows the ADAFRUIT convention
    # → pin 1 = GND (−), pin 2 = + (BAT_P). Silk +/- on the PCB. NOTE:
    # vendor-dependent — verify the battery wiring with a multimeter (the
    # battery now mates via a wire/JST-to-header pigtail).
    sch.components.add(lib_id="Connector_Generic:Conn_01x02",
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                       footprint="Connector_PinHeader_2.54mm:PinHeader_1x02_P2.54mm_Vertical")
    auto_label(sch, "J1", {
        "1": ("GND",   "left"),   # Adafruit pin 1 = GND
        "2": ("BAT_P", "left"),   # Adafruit pin 2 = +
    })

    # SW1 — armament / battery disconnect (SPDT slide)
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    })

    # J2 — external switch / jumper header (parallel to SW1)
    # Pin 1 = BAT_P (input side), Pin 2 = BAT_SW (output side).
    # Closing a jumper across J2 bypasses SW1 (system always-on).
    sch.components.add(lib_id="Connector_Generic:Conn_01x02",
                       reference="J2", value="ext_switch_header",
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    # J5 — switched-battery OUTPUT (1x02 pin header, v0.1.3; was a vertical
    # JST-PH in v0.1.2). Carries the switched rail BAT_SW and GND to the XIAO
    # BAT pads. v0.1.3: back to a pin header (frees space) + moved to the
    # service edge. Polarity: pin 1 = GND (−), pin 2 = + (BAT_SW).
    sch.components.add(lib_id="Connector_Generic:Conn_01x02",
                       reference="J5", value="LiPo_out_hdr",
                       position=g(130, 80),
                       footprint="Connector_PinHeader_2.54mm:PinHeader_1x02_P2.54mm_Vertical")
    auto_label(sch, "J5", {
        "1": ("GND",    "right"),  # Adafruit pin 1 = GND
        "2": ("BAT_SW", "right"),  # Adafruit pin 2 = +
    })

    # ==================================================================
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
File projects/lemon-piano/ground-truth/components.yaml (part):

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  KEYS_HEADER:
    refs: [J2]
    mount_side: top
    source: "docs/NETLIST.md — pin1=GND (west, above A7), then KEY7..KEY1"
    pins:
      "J2.1": {func: GND_CLIP, net: /GND}
      "J2.2": {func: KEY7, net: /KEY7}
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    source: "v5 HARDWARE.md — 220R pull-up per key, pin->R->+5V"
    pins:
      "R1.1": {func: rail, net: /+5V}
      "R1.2": {func: pin,  net: /KEY1}
      "R2.1": {func: rail, net: /+5V}
      "R2.2": {func: pin,  net: /KEY2}
      "R3.1": {func: rail, net: /+5V}
      "R3.2": {func: pin,  net: /KEY3}
      "R4.1": {func: rail, net: /+5V}
      "R4.2": {func: pin,  net: /KEY4}
      "R5.1": {func: rail, net: /+5V}
      "R5.2": {func: pin,  net: /KEY5}
      "R6.1": {func: rail, net: /+5V}
      "R6.2": {func: pin,  net: /KEY6}
      "R7.1": {func: rail, net: /+5V}
      "R7.2": {func: pin,  net: /KEY7}

  SENS_MINUS_PULLUP:
    refs: [R18]
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    source: "v5 HARDWARE.md — A7 has no internal pull-up: external 10k to +5V"
    pins:
      "R18.1": {func: rail, net: /+5V}
      "R18.2": {func: pin,  net: /SENS_MINUS}

  # ────────────────────────────────────────────────────────────────────
  # LED bar: LED n anode <- pin n+1, cathode -> 220R -> GND
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    mount_side: top
    source: "v5 HARDWARE.md — SENS+ D12 to GND (internal pull-up); SENS- A7 to GND (R18)"
    pins:
      "SW1.1": {func: pin, net: /SENS_PLUS}
      "SW1.2": {func: gnd, net: /GND}
      "SW2.1": {func: pin, net: /SENS_MINUS}
      "SW2.2": {func: gnd, net: /GND}

  MOUNTING:
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
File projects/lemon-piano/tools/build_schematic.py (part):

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    sch.components.add(lib_id="Device:D_Schottky", reference="D2", value="1N5817",
                       position=g(60, 40),
                       footprint="Diode_THT:D_DO-41_SOD81_P5.08mm_Vertical_AnodeUp")
    auto_label(sch, "D2", {"1": ("VRAW", "right"), "2": ("VIN", "left")})

    sch.components.add(lib_id="Device:C_Polarized", reference="C1", value="470uF/16V",
                       position=g(75, 50),
                       footprint="Capacitor_THT:CP_Radial_D8.0mm_P3.50mm")
    auto_label(sch, "C1", {"1": ("VRAW", "up"), "2": ("GND", "down")})

    sch.components.add(lib_id="Device:C", reference="C2", value="100nF",
                       position=g(85, 50), footprint=C_FP)
    auto_label(sch, "C2", {"1": ("VRAW", "up"), "2": ("GND", "down")})

    sch.components.add(lib_id="Device:L", reference="L1", value="100uH",
                       position=g(95, 40),
                       footprint="Inductor_THT:L_Radial_D8.7mm_P5.00mm_Fastron_07HCP")
    auto_label(sch, "L1", {"1": ("VRAW", "left"), "2": ("+5V", "right")})

    sch.components.add(lib_id="Device:C_Polarized", reference="C3", value="470uF/16V",
                       position=g(105, 50),
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        auto_label(sch, f"R{i}", {"1": ("+5V", "up"), "2": (f"KEY{i}", "down")})
    sch.components.add(lib_id="Device:R", reference="R18", value="10k",
                       position=g(140 + 12 * 7, 40), footprint=R_FP)
    auto_label(sch, "R18", {"1": ("+5V", "up"), "2": ("SENS_MINUS", "down")})

    # ── LED bar + series resistors ──────────────────────────────────────
    for i in range(1, 11):
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    sch.components.add(lib_id="Device:Buzzer", reference="BUZ1",
                       value="passive_buzzer", position=g(30, 80),
                       footprint="Buzzer_Beeper:Buzzer_12x9.5RM7.6")
    auto_label(sch, "BUZ1", {"1": ("BUZZER", "left"), "2": ("GND", "left")})

    sch.components.add(lib_id="Switch:SW_Push", reference="SW1", value="SENS+",
                       position=g(30, 95),
                       footprint="Button_Switch_THT:SW_PUSH_6mm")
    auto_label(sch, "SW1", {"1": ("SENS_PLUS", "left"), "2": ("GND", "right")})

    sch.components.add(lib_id="Switch:SW_Push", reference="SW2", value="SENS-",
                       position=g(30, 110),
                       footprint="Button_Switch_THT:SW_PUSH_6mm")
    auto_label(sch, "SW2", {"1": ("SENS_MINUS", "left"), "2": ("GND", "right")})

    # ── PWR_FLAGs: VIN is sourced by J1; +5V by the choke; GND by J1.2 ──
    add_pwr_flag(sch, (30, 25), "VIN", "01")
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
